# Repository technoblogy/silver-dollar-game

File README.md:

# Silver Dollar Game
A logic game in which the aim is move five silver dollars, represented by LEDs, along a strip of 12 positions. You take turns with the game, and the last player able to move wins.

For more information see <http://www.technoblogy.com/show?4KA5>.

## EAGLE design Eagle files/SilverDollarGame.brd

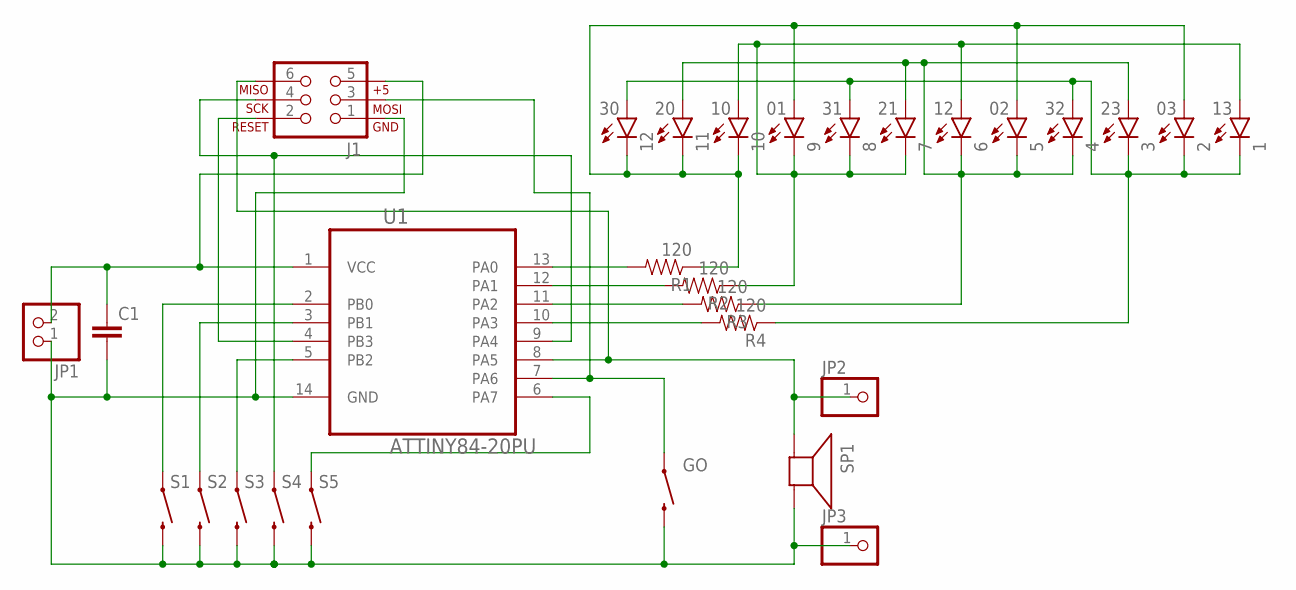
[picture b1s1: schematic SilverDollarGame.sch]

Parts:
1, 2, 3, 4, 5, 6, 7, 8, 9, 10, 11, 12: LED3MM
C1: 0.1UF-50V-20%(PTH)KIT-EZ; CAP-PTH-SMALL-KIT
GO: SWITCH-MOMENTARY-2PTH; TACTILE-PTH
J1: AVR_SPI_PRG_6TESTPOINTS; 2X3_TEST_POINTS
JP1: HEADER-1X2ROUND; 1X02_ROUND
JP2, JP3: PINHD-1X1CB; 1X01-CLEANBIG
R1, R2, R3, R4: 120; AXIAL-0.3
S1, S2, S3, S4, S5: SWITCH-MOMENTARY-2PTH; TACTILE-PTH
SP1: ABT-402-RC; AL60P
U1: ATTINY84-20PU; DIP254P762X533-14

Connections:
unnamed: R3.P$2 (2), U1.11 (PA2)
unnamed: R4.P$2 (2), U1.10 (PA3)
unnamed: C1.1, J1.5, JP1.2, U1.1 (VCC)
unnamed: R1.P$2 (2), U1.13 (PA0)
unnamed: 2.A, 5.A, 9.A, 10.K (C), 11.K (C), 12.K (C), R1.P$1 (1)
unnamed: R2.P$2 (2), U1.12 (PA1)
unnamed: 3.A, 4.K (C), 5.K (C), 6.K (C), 7.A, 11.A, R3.P$1 (1)
unnamed: C1.2, GO.3 (2), J1.1, JP1.1, JP3.1, S1.3 (2), S2.3 (2), S3.3 (2), S4.3 (2), S5.3 (2), SP1.2 (-), U1.14 (GND)
unnamed: 1.A, 6.A, 7.K (C), 8.K (C), 9.K (C), 10.A, R2.P$1 (1)
unnamed: S1.1, U1.2 (PB0)
unnamed: GO.1, J1.3, U1.7 (PA6)
unnamed: J1.2, U1.4 (PB3)
unnamed: S2.1, U1.3 (PB1)
unnamed: S3.1, U1.5 (PB2)
unnamed: S5.1, U1.6 (PA7)
unnamed: J1.6, JP2.1, SP1.1 (+), U1.8 (PA5)
unnamed: J1.4, S4.1, U1.9 (PA4)
unnamed: 1.K (C), 2.K (C), 3.K (C), 4.A, 8.A, 12.A, R4.P$1 (1)

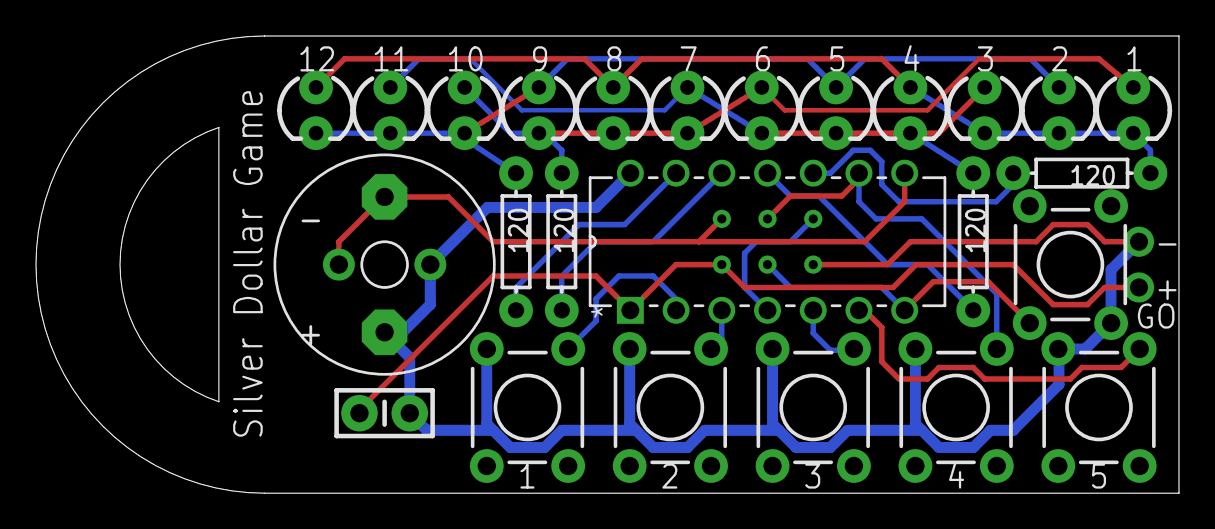
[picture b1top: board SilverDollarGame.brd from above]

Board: 2 copper layers, 63.5 x 25.4 mm, 29 parts (1 on the bottom side), 18 nets.

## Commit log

2023-12-08 Version 1 - 8th December 2023

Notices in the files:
parts and their libraries:
SparkFun-LED: Licensing: Creative Commons ShareAlike 4.0 International - https://creativecommons.org/licenses/by-sa/4.0
microbuilder: This work is placed in the public domain, and may be freely used for commercial and non-commercial work with the following conditions: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
